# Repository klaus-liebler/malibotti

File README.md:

# Malibotti
Malibotti represents my initial effort to develop a drawing robot, building upon the concepts of the [ESP32-Drawing-Robot project](https://github.com/MatixYo/ESP32-Drawing-Robot). Key differentiators include a reduced reliance on 3D-printed parts and a custom PCB that functions dually as an electronic carrier and a mechanical structure. Additionally, a dedicated daughterboard with high-precision Hall-effect sensors provides servo arm position data, facilitating closed-loop feedback control for 360° servos.

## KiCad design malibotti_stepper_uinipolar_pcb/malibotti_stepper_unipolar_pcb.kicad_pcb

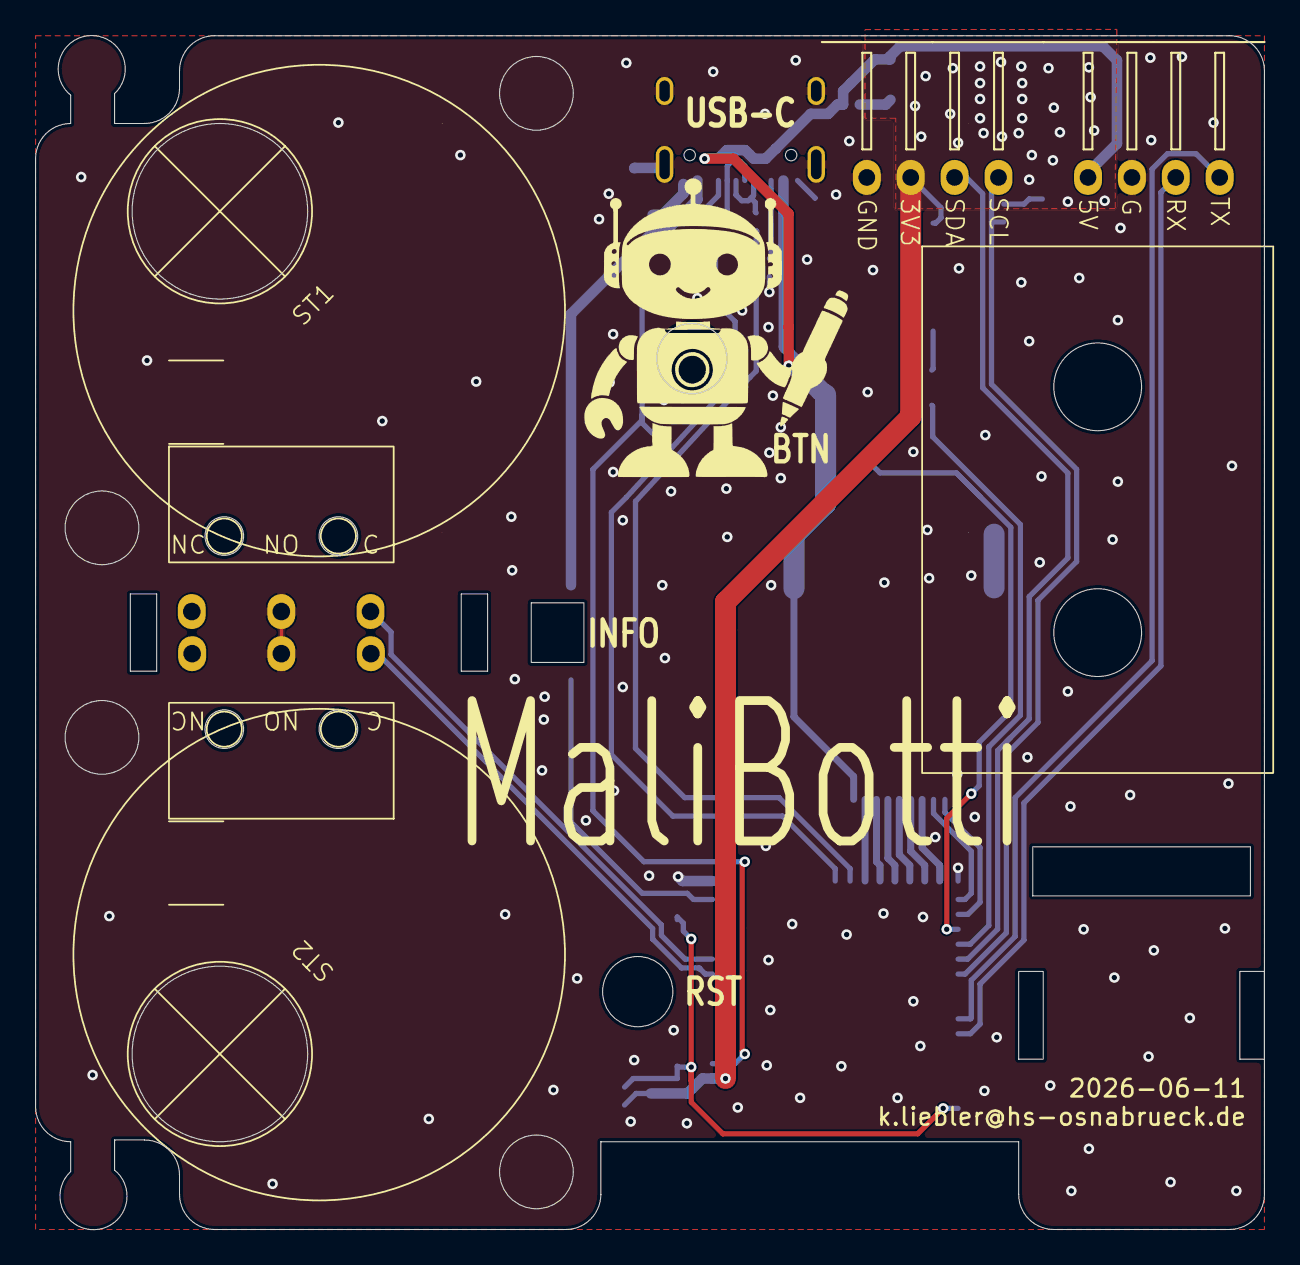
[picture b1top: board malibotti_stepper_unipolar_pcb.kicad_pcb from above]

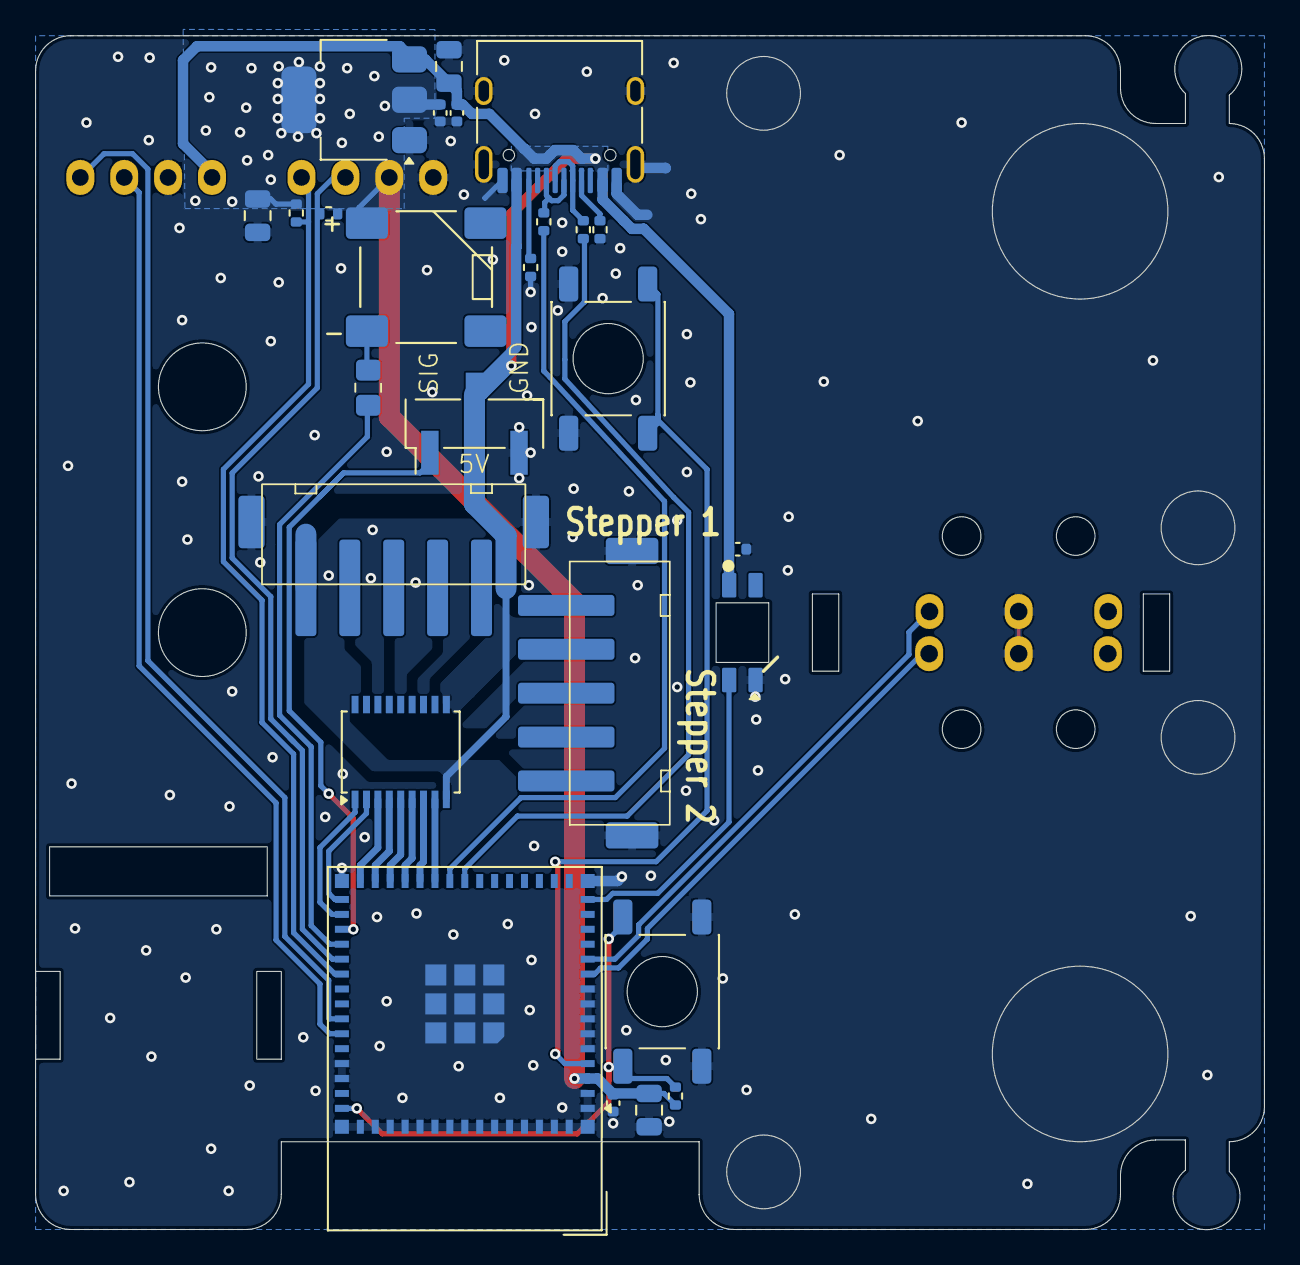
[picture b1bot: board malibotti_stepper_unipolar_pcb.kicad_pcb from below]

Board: 2 copper layers, 70.0 x 68.0 mm, 34 parts (26 on the bottom side), 37 nets.

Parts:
BZ1: Buzzer; XDCR_CMT-7525-80-SMT-TR_handsolder
C3, C9, C10, C11: u1; C_0402_1005Metric
C5, C6, C12: 22u; C_0805_2012Metric
D21: RGB3; SK6812MINI-E_REV
H1: Hinge3040; Hinge_3040
J1: Stepper 1; JST_XH_5P_SMD
J2: Stepper 2; JST_XH_5P_SMD
J3: Servo; PinHeader_1x03_P2.54mm_Vertical_SMD_Pin1Left
J4: I2C; JST_XH_S4B-XH-A-1_1x04_P2.50mm_Horizontal_SmallerCourtyard
J5: USB_C_Receptacle_USB2.0_16P; USB_C_Receptacle_HRO_TYPE-C-31-M-12
J6: Serial; JST_XH_S4B-XH-A-1_1x04_P2.50mm_Horizontal_SmallerCourtyard
R1, R3, R4, R7, R26: 5k1; R_0402_1005Metric
R2: 100R; R_0805_2012Metric_Pad1.20x1.40mm_HandSolder
R8, R9: 22R; R_0402_1005Metric
SRV1: Servo SG90; SG90_vertical_PCB
ST1: Stepper 1; 28BYJ-48
ST2: Stepper 2; 28BYJ-48
SW1: RST; SW_Push_1P1T_NO_6x6mm_H6.5mm_Reverse
SW2: MicroSwitchLeft; Omron D2F Left Angled
SW3: MicroSwitchRight; Omron D2F Right Angled
SW8: BTN; SW_Push_1P1T_NO_6x6mm_H6.5mm_Reverse
U1: TBD62783A; SSOP-18_4.4x6.5mm_P0.65mm
U3: AMS1117; SOT-223-3_TabPin2
U5: ESP32-S3-MINI-1; ESP32-S2-MINI-1

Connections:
+3V3: BZ1.P (+), C6.1, C10.1, C11.1, C12.1, J4.3, R3.2, R4.2, R26.2, U3.2 (VO), U5.3 (3V3)
+5V: C3.1, C5.1, C9.1, D21.1 (VDD), J3.2, J5.A4 (VBUS), J5.A9 (VBUS), J5.B4 (VBUS), J5.B9 (VBUS), J6.4, U1.9 (VCC), U3.3 (VI)
/RX: J6.2, U5.40 (RXD0)
/TX: J6.1, U5.39 (TXD0)
/USBD+: R8.2, U5.24 (USB_D+)
/USBD-: R9.2, U5.23 (USB_D-)
BUZZER: R2.2, U5.34 (IO38)
GND: C3.2, C5.2, C6.2, C9.2, C10.2, C11.2, C12.2, D21.3 (GND), J1.1, J1.MP (MountPin), J2.1, J2.MP (MountPin), J3.3, J4.4, J5.A1 (GND), J5.A12 (GND), J5.B1 (GND), J5.B12 (GND), J5.SH (SHIELD), J6.3, R1.2, R7.2, SW1.2, SW2.2 (C), SW3.2 (C), SW8.1, U1.10 (GND), U3.1 (GND), U5.1 (GND), U5.2 (GND), U5.5 (IO1), U5.6 (IO2), U5.7 (IO3), U5.8 (IO4), U5.9 (IO5), U5.42 (GND), U5.43 (GND), U5.46 (GND), U5.47 (GND), U5.48 (GND), U5.49 (GND), U5.50 (GND), U5.51 (GND), U5.52 (GND), U5.53 (GND), U5.54 (GND), U5.55 (GND), U5.56 (GND), U5.57 (GND), U5.58 (GND), U5.59 (GND), U5.60 (GND), U5.61 (GND), U5.62 (GND), U5.63 (GND), U5.64 (GND), U5.65 (GND)
LIMIT_LEFT: SW2.1 (B), U5.11 (IO7)
LIMIT_RIGHT: SW3.1 (B), U5.10 (IO6)
unnamed: BZ1.N (-), R2.1
unnamed: J1.2, U1.17 (O2)
unnamed: J1.3, U1.15 (O4)
unnamed: J1.4, U1.13 (O6)
unnamed: J1.5, U1.11 (O8)
unnamed: J2.2, U1.12 (O7)
unnamed: J2.3, U1.14 (O5)
unnamed: J2.4, U1.16 (O3)
unnamed: J2.5, U1.18 (O1)
unnamed: J5.A5 (CC1), R1.1
unnamed: J5.B5 (CC2), R7.1
unnamed: J5.A6 (D+), J5.B6 (D+), R8.1
unnamed: J5.A7 (D-), J5.B7 (D-), R9.1
unnamed: R26.1, SW1.1, U5.45 (EN)
unnamed: SW8.2, U5.4 (IO0)
RGB_LED: D21.4 (DIN), U5.15 (IO11)
SCL: J4.1, R3.1, U5.36 (IO40)
SDA: J4.2, R4.1, U5.35 (IO39)
STEPPER1_PH1: U1.8 (I8), U5.25 (IO21)
STEPPER1_PH2: U1.6 (I6), U5.27 (IO47)
STEPPER1_PH3: U1.4 (I4), U5.29 (IO34)
STEPPER1_PH4: U1.2 (I2), U5.31 (IO35)
STEPPER2_PH1: U1.1 (I1), U5.32 (IO36)
STEPPER2_PH2: U1.3 (I3), U5.30 (IO48)
STEPPER2_PH3: U1.5 (I5), U5.28 (IO33)
STEPPER2_PH4: U1.7 (I7), U5.26 (IO26)
Servo1: J3.1, U5.33 (IO37)

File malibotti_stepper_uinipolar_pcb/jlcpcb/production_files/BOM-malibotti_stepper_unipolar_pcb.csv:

Comment,Designator,Footprint,LCSC,Quantity
100R,R2,R_0805_2012Metric_Pad1.20x1.40mm_HandSolder,C17408,1
22R,"R8,R9",R_0402_1005Metric,C25092,2
22u,"C12,C5,C6",C_0805_2012Metric,C45783,3
5k1,"R1,R26,R3,R4,R7",R_0402_1005Metric,C25905,5
AMS1117,U3,SOT-223-3_TabPin2,C6186,1
BTN,SW8,SW_Push_1P1T_NO_6x6mm_H6.5mm_Reverse,C541960,1
Buzzer,BZ1,XDCR_CMT-7525-80-SMT-TR_handsolder,C49246950,1
ESP32-S3-MINI-1,U5,ESP32-S2-MINI-1,C2913206,1
RGB3,D21,SK6812MINI-E_REV,C5149201,1
RST,SW1,SW_Push_1P1T_NO_6x6mm_H6.5mm_Reverse,C541960,1
Servo,J3,PinHeader_1x03_P2.54mm_Vertical_SMD_Pin1Left,C5160786,1
Stepper 1,J1,JST_XH_5P_SMD,C7429683,1
Stepper 2,J2,JST_XH_5P_SMD,C7429683,1
TBD62783A,U1,SSOP-18_4.4x6.5mm_P0.65mm,C4153829,1
USB_C_Receptacle_USB2.0_16P,J5,USB_C_Receptacle_HRO_TYPE-C-31-M-12,C165948,1
u1,"C10,C11,C3,C9",C_0402_1005Metric,C1525,4
MicroSwitchLeft,SW2,Omron D2F Left Angled,,1
Serial,J6,JST_XH_S4B-XH-A-1_1x04_P2.50mm_Horizontal_SmallerCourtyard,,1
MicroSwitchRight,SW3,Omron D2F Right Angled,,1
I2C,J4,JST_XH_S4B-XH-A-1_1x04_P2.50mm_Horizontal_SmallerCourtyard,,1

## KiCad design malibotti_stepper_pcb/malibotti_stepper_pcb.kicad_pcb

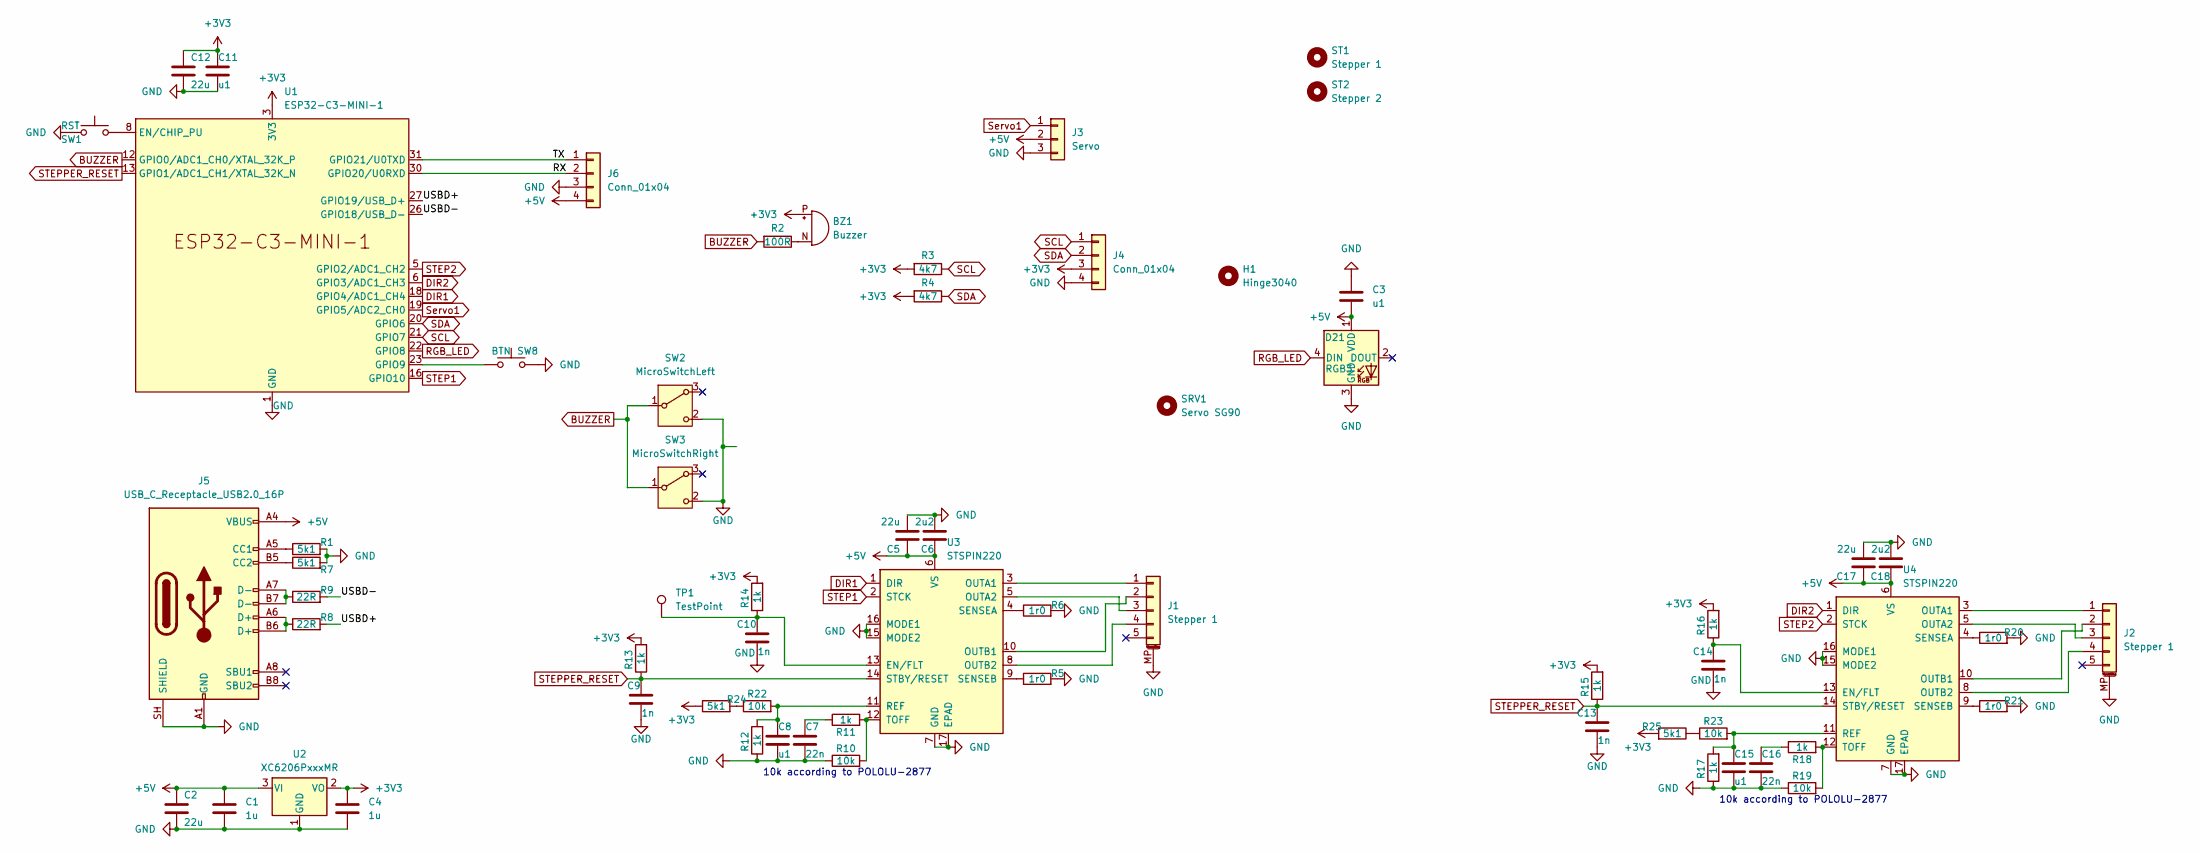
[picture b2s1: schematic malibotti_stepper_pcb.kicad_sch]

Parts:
BZ1: Buzzer; XDCR_CMT-7525-80-SMT-TR_handsolder
C1, C4: 1u; C_0402_1005Metric
C2, C5, C12, C17: 22u; C_0805_2012Metric
C3, C8, C11, C15: u1; C_0402_1005Metric
C6, C18: 2u2; C_0603_1608Metric
C7, C16: 22n; C_0402_1005Metric
C9, C10, C13, C14: 1n; C_0402_1005Metric
D21: RGB3; SK6812MINI-E_REV; MPN SK6812MINI-EA
H1: Hinge3040; Hinge_3040
J1, J2: Stepper 1; JST_XH_5P_SMD
J3: Servo; PinHeader_1x03_P2.54mm_Vertical_SMD_Pin1Left
J4, J6: Conn_01x04; JST_XH_S4B-XH-A-1_1x04_P2.50mm_Horizontal_SmallerCourtyard
J5: USB_C_Receptacle_USB2.0_16P; USB_C_Receptacle_HRO_TYPE-C-31-M-12
R1, R7, R24, R25: 5k1; R_0402_1005Metric
R2: 100R; R_0805_2012Metric_Pad1.20x1.40mm_HandSolder
R3, R4: 4k7; R_0402_1005Metric
R5, R6, R20, R21: 1r0; R_0805_2012Metric_Pad1.20x1.40mm_HandSolder
R8, R9: 22R; R_0402_1005Metric
R10, R19, R22, R23: 10k; R_0402_1005Metric
R11, R12, R13, R14, R15, R16, R17, R18: 1k; R_0402_1005Metric
SRV1: Servo SG90; SG90_vertical_PCB
ST1: Stepper 1; 28BYJ-48
ST2: Stepper 2; 28BYJ-48
SW1: RST; SW_Push_1P1T_NO_6x6mm_H6.5mm_Reverse; MPN TS-1095E-A6B3-D2
SW2: MicroSwitchLeft; Omron D2F Left Angled
SW3: MicroSwitchRight; Omron D2F Right Angled
SW8: BTN; SW_Push_1P1T_NO_6x6mm_H6.5mm_Reverse; MPN TS-1095E-A6B3-D2
TP1: TestPoint; TestPoint_Loop_D1.80mm_Drill1.0mm_Beaded
U1: ESP32-C3-MINI-1
U2: XC6206PxxxMR; SOT-23-3
U3, U4: STSPIN220; VQFN-16-1EP_3x3mm_P0.5mm_EP1.8x1.8mm

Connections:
+3V3: BZ1.P (+), C4.1, C11.1, C12.1, J4.3, R3.2, R4.2, R13.2, R14.2, R15.2, R16.2, R24.1, R25.2, U1.3 (3V3), U2.2 (VO); also elsewhere on the board
+5V: C1.1, C2.1, C3.1, C5.1, C6.1, C17.1, C18.1, D21.1 (VDD), J3.2, J5.A4 (VBUS), J5.A9 (VBUS), J5.B4 (VBUS), J5.B9 (VBUS), J6.4, U2.3 (VI), U3.6 (VS), U4.6 (VS)
/RX: J6.2, U1.30 (GPIO20/U0RXD)
/TX: J6.1, U1.31 (GPIO21/U0TXD)
/USBD+: R8.2, U1.27 (GPIO19/USB_D+)
/USBD-: R9.2, U1.26 (GPIO18/USB_D-)
BUZZER: R2.2, SW2.1 (B), SW3.1 (B), U1.12 (GPIO0/ADC1_CH0/XTAL_32K_P)
DIR1: U1.18 (GPIO4/ADC1_CH4), U3.1 (DIR)
DIR2: U1.6 (GPIO3/ADC1_CH3), U4.1 (DIR)
GND: C1.2, C2.2, C3.2, C4.2, C5.2, C6.2, C7.2, C8.2, C9.2, C10.2, C11.2, C12.2, C13.2, C14.2, C15.2, C16.2, C17.2, C18.2, D21.3 (GND), J1.MP (MountPin), J2.MP (MountPin), J3.3, J4.4, J5.A1 (GND), J5.A12 (GND), J5.B1 (GND), J5.B12 (GND), J5.SH (SHIELD), J6.3, R1.2, R5.2, R6.2, R7.2, R10.1, R12.1, R17.1, R19.1, R20.2, R21.2, SW1.2, SW2.2 (C), SW3.2 (C), SW8.2, U1.1 (GND), U1.2 (GND), U1.11 (GND), U1.14 (GND), U1.36 (GND), U1.37 (GND), U1.38 (GND), U1.39 (GND), U1.40 (GND), U1.41 (GND), U1.42 (GND), U1.43 (GND), U1.44 (GND), U1.45 (GND), U1.46 (GND), U1.47 (GND), U1.48 (GND), U1.49 (GND), U1.50 (GND), U1.51 (GND), U1.52 (GND), U1.53 (GND), U2.1 (GND), U3.7 (GND), U3.15 (MODE2), U3.16 (MODE1), U3.17 (EPAD), U4.7 (GND), U4.15 (MODE2), U4.16 (MODE1), U4.17 (EPAD)
unnamed: BZ1.N (-), R2.1
unnamed: C7.1, R11.1
unnamed: C16.1, R18.1
unnamed: J1.1, U3.3 (OUTA1)
unnamed: J1.2, U3.10 (OUTB1)
unnamed: J1.3, U3.5 (OUTA2)
unnamed: J1.4, U3.8 (OUTB2)
unnamed: J2.1, U4.3 (OUTA1)
unnamed: J2.2, U4.10 (OUTB1)
unnamed: J2.3, U4.5 (OUTA2)
unnamed: J2.4, U4.8 (OUTB2)
unnamed: J5.A5 (CC1), R1.1
unnamed: J5.B5 (CC2), R7.1
unnamed: J5.A6 (D+), J5.B6 (D+), R8.1
unnamed: J5.A7 (D-), J5.B7 (D-), R9.1
unnamed: R22.1, R24.2
unnamed: R23.1, R25.1
unnamed 27: SW1.1, U1.8 (EN/CHIP_PU); also elsewhere on the board
unnamed: SW8.1, U1.23 (GPIO9)
unnamed: C10.1, R14.1, TP1.1 (1_1), U3.13 (EN/FLT)
unnamed: C8.1, R12.2, R22.2, U3.11 (REF)
unnamed: R6.1, U3.4 (SENSEA)
unnamed: R5.1, U3.9 (SENSEB)
unnamed: R10.2, R11.2, U3.12 (TOFF)
unnamed: C14.1, R16.1, U4.13 (EN/FLT)
unnamed: C15.1, R17.2, R23.2, U4.11 (REF)
unnamed: R20.1, U4.4 (SENSEA)
unnamed: R21.1, U4.9 (SENSEB)
unnamed: R18.2, R19.2, U4.12 (TOFF)
RGB_LED: D21.4 (DIN), U1.22 (GPIO8)
SCL: J4.1, R3.1, U1.21 (GPIO7)
SDA: J4.2, R4.1, U1.20 (GPIO6)
STEP1: U1.16 (GPIO10), U3.2 (STCK)
STEP2: U1.5 (GPIO2/ADC1_CH2), U4.2 (STCK)
STEPPER_RESET: C9.1, C13.1, R13.1, R15.1, U1.13 (GPIO1/ADC1_CH1/XTAL_32K_N), U3.14 (STBY/RESET), U4.14 (STBY/RESET)
Servo1: J3.1, U1.19 (GPIO5/ADC2_CH0)

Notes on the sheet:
10k according to POLOLU-2877

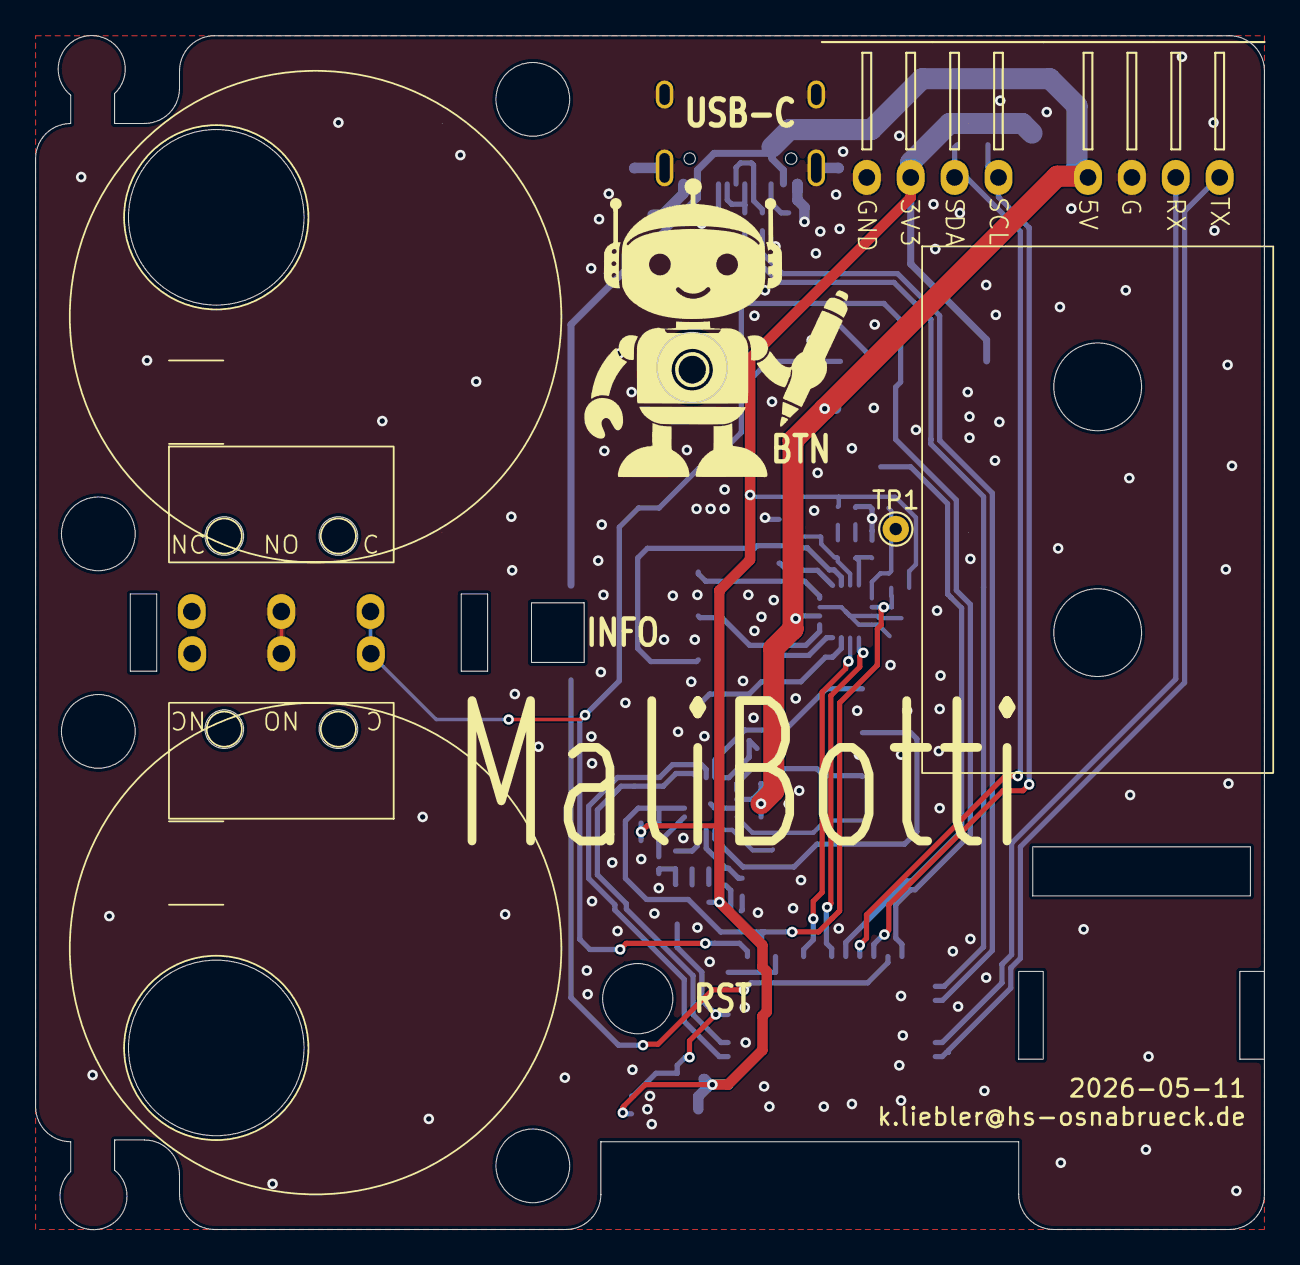
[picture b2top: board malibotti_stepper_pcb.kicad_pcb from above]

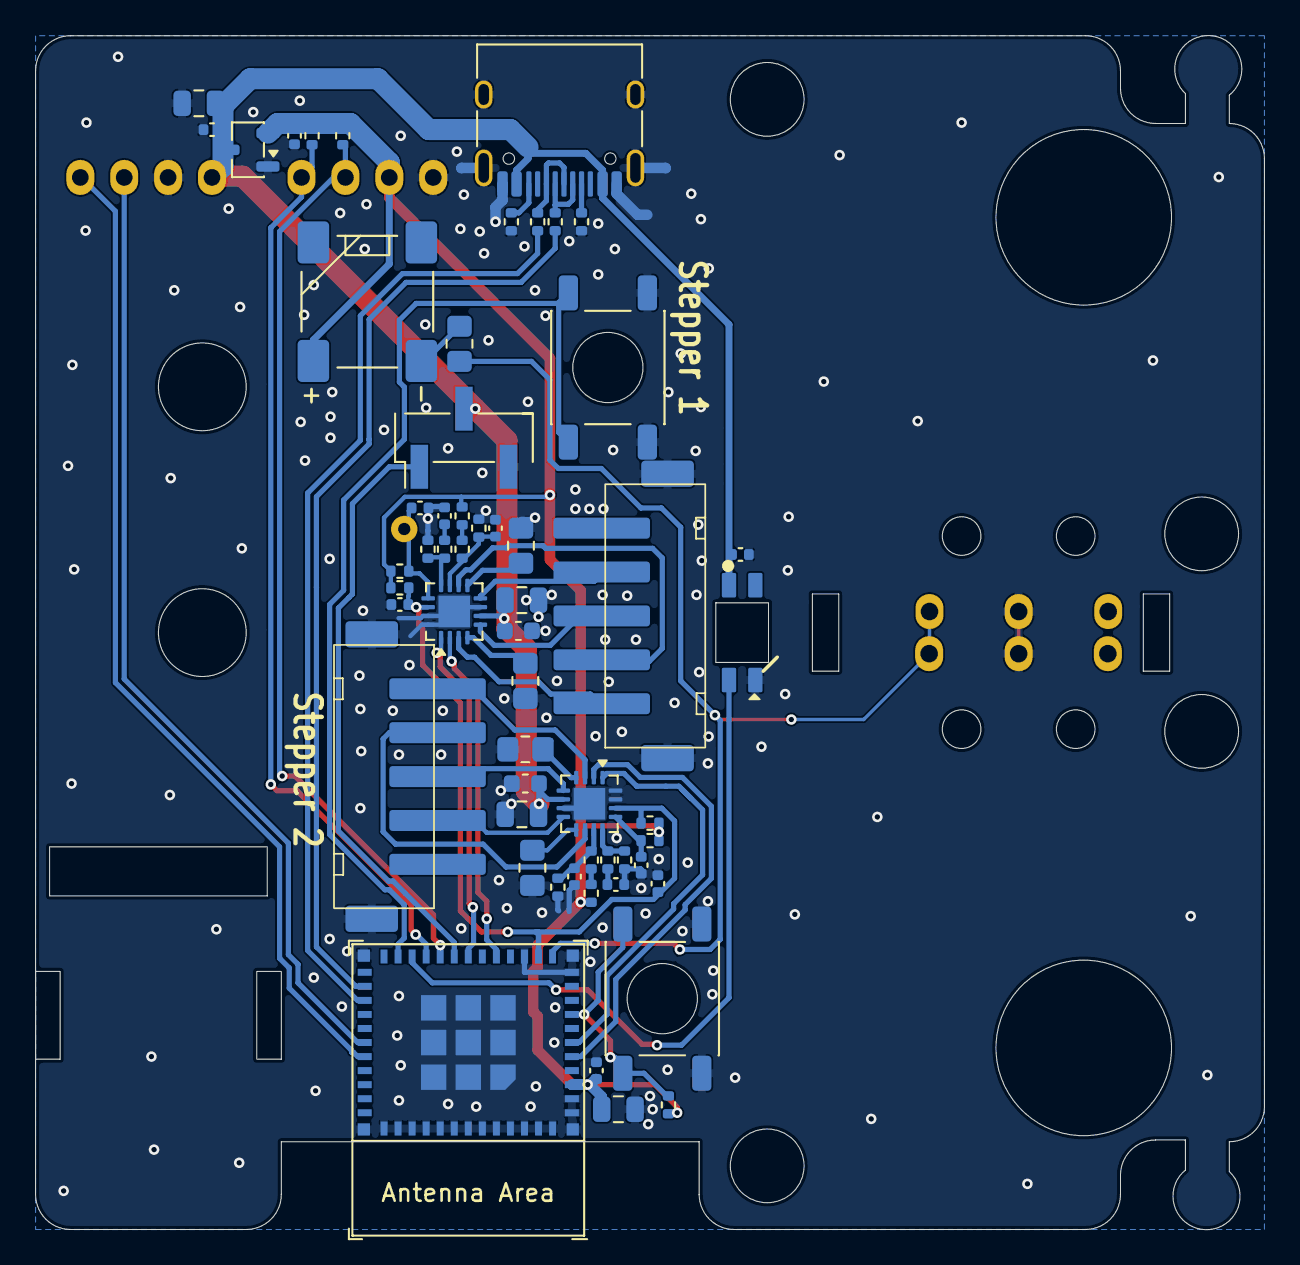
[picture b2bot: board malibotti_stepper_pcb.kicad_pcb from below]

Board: 2 copper layers, 70.0 x 68.0 mm, 65 parts (55 on the bottom side), 46 nets.

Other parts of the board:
R26: 10k; R_0402_1005Metric

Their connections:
+3V3: R26.2; also elsewhere on the board
unnamed 27: R26.1; also elsewhere on the board

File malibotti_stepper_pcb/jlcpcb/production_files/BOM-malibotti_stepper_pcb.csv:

Comment,Designator,Footprint,LCSC,Quantity
100R,R2,R_0805_2012Metric_Pad1.20x1.40mm_HandSolder,C17408,1
10k,"R10,R19,R22,R23",R_0402_1005Metric,C25744,4
1k,"R11,R12,R13,R14,R15,R16,R17,R18",R_0402_1005Metric,C11702,8
1n,"C10,C13,C14,C9",C_0402_1005Metric,C1523,4
1r0,"R20,R21,R5,R6",R_0805_2012Metric_Pad1.20x1.40mm_HandSolder,C25271,4
1u,"C1,C4",C_0402_1005Metric,C52923,2
22R,"R8,R9",R_0402_1005Metric,C25092,2
22n,"C16,C7",C_0402_1005Metric,C1532,2
22u,"C12,C17,C2,C5",C_0805_2012Metric,C45783,4
2u2,"C18,C6",C_0603_1608Metric,C23630,2
4k7,"R3,R4",R_0402_1005Metric,C25900,2
5k1,"R1,R24,R25,R7",R_0402_1005Metric,C25905,4
BTN,SW8,SW_Push_1P1T_NO_6x6mm_H6.5mm_Reverse,C541960,1
Buzzer,BZ1,XDCR_CMT-7525-80-SMT-TR_handsolder,C49246950,1
ESP32-C3-MINI-1,U1,ESP32-C3-MINI-1,C2838502,1
RGB3,D21,SK6812MINI-E_REV,C5149201,1
RST,SW1,SW_Push_1P1T_NO_6x6mm_H6.5mm_Reverse,C541960,1
STSPIN220,"U3,U4",VQFN-16-1EP_3x3mm_P0.5mm_EP1.8x1.8mm,C2150516,2
Servo,J3,PinHeader_1x03_P2.54mm_Vertical_SMD_Pin1Left,C5160786,1
Stepper 1,"J1,J2",JST_XH_5P_SMD,C7429683,2
USB_C_Receptacle_USB2.0_16P,J5,USB_C_Receptacle_HRO_TYPE-C-31-M-12,C165948,1
XC6206PxxxMR,U2,SOT-23-3,C5446,1
u1,"C11,C15,C3,C8",C_0402_1005Metric,C1525,4
MicroSwitchLeft,SW2,Omron D2F Left Angled,,1
Conn_01x04,J6,JST_XH_S4B-XH-A-1_1x04_P2.50mm_Horizontal_SmallerCourtyard,,1
MicroSwitchRight,SW3,Omron D2F Right Angled,,1
Conn_01x04,J4,JST_XH_S4B-XH-A-1_1x04_P2.50mm_Horizontal_SmallerCourtyard,,1
TestPoint,TP1,TestPoint_THTPad_D1.0mm_Drill0.5mm,,1

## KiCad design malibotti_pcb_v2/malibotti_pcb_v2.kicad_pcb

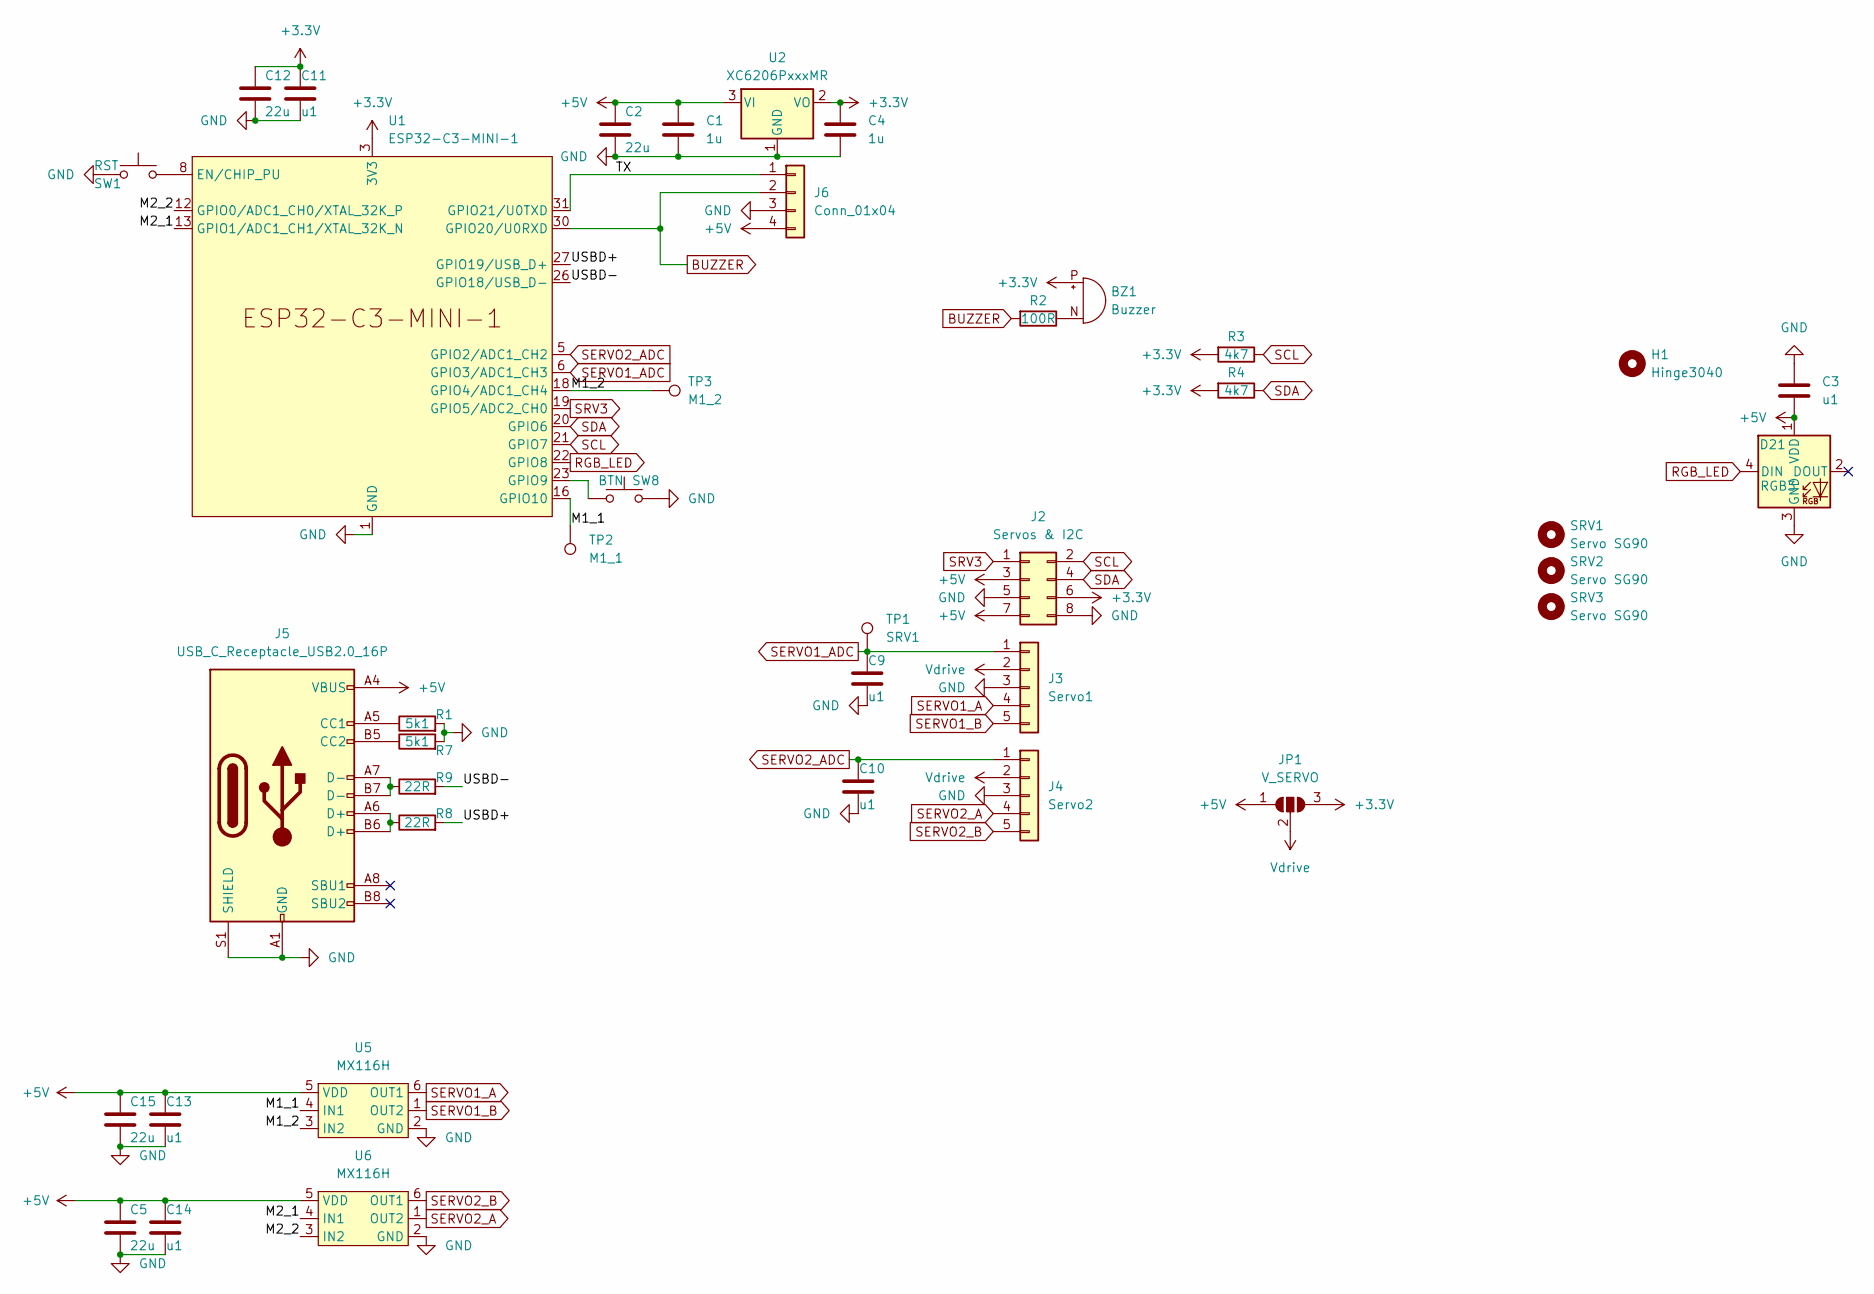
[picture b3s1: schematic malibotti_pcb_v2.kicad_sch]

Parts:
BZ1: Buzzer; XDCR_CMT-7525-80-SMT-TR_handsolder
C1, C4: 1u; C_0402_1005Metric
C2, C5, C12, C15: 22u; C_0603_1608Metric
C3, C11, C13, C14: u1; C_0402_1005Metric
C9, C10: u1; C_0805_2012Metric_Pad1.18x1.45mm_HandSolder
D21: RGB3; SK6812MINI-E_REV; MPN SK6812MINI-EA
H1: Hinge3040; Hinge_3040
J2: Servos & I2C; PinHeader_2x04_P2.54mm_Vertical_SMD
J3: Servo1; JST_XH_B5B-XH-A_1x05_P2.50mm_Vertical
J4: Servo2; JST_XH_B5B-XH-A_1x05_P2.50mm_Vertical
J5: USB_C_Receptacle_USB2.0_16P; USB_C_Receptacle_HRO_TYPE-C-31-M-12
J6: Conn_01x04; JST_XH_S4B-XH-A-1_1x04_P2.50mm_Horizontal_SmallerCourtyard
JP1: V_SERVO; SolderJumper-3_P1.3mm_Bridged2Bar12_RoundedPad1.0x1.5mm_Num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
R1, R7: 5k1; R_0402_1005Metric
R2: 100R; R_0805_2012Metric_Pad1.20x1.40mm_HandSolder
R3, R4: 4k7; R_0402_1005Metric
R8, R9: 22R; R_0402_1005Metric
SRV1, SRV2: Servo SG90; SG90_PCB
SRV3: Servo SG90; SG90_vertical_PCB
SW1: RST; SW_Push_1P1T_NO_6x6mm_H6.5mm_Reverse; MPN TS-1095E-A6B3-D2
SW8: BTN; SW_Push_1P1T_NO_6x6mm_H6.5mm_Reverse; MPN TS-1095E-A6B3-D2
TP1: SRV1; TestPoint_Pad_1.5x1.5mm
TP2: M1_1; TestPoint_Pad_1.5x1.5mm
TP3: M1_2; TestPoint_Pad_1.5x1.5mm
U1: ESP32-C3-MINI-1
U2: XC6206PxxxMR; SOT-23-3
U5, U6: MX116H; SOT-23-6

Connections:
+3.3V: BZ1.P (+), C4.1, C11.1, C12.1, J2.6, JP1.3 (B), R3.2, R4.2, U1.3 (3V3), U2.2 (VO)
+5V: C1.1, C2.1, C3.1, C5.1, C13.1, C14.1, C15.1, D21.1 (VDD), J2.3, J2.7, J5.A4 (VBUS), J5.A9 (VBUS), J5.B4 (VBUS), J5.B9 (VBUS), J6.4, JP1.1 (A), U2.3 (VI), U5.5 (VDD), U6.5 (VDD)
/M1_1: TP2.1, U1.16 (GPIO10), U5.4 (IN1)
/M1_2: TP3.1, U1.18 (GPIO4/ADC1_CH4), U5.3 (IN2)
/M2_1: U1.13 (GPIO1/ADC1_CH1/XTAL_32K_N), U6.4 (IN1)
/M2_2: U1.12 (GPIO0/ADC1_CH0/XTAL_32K_P), U6.3 (IN2)
/TX: J6.1, U1.31 (GPIO21/U0TXD)
/USBD+: R8.2, U1.27 (GPIO19/USB_D+)
/USBD-: R9.2, U1.26 (GPIO18/USB_D-)
BUZZER: J6.2, R2.2, U1.30 (GPIO20/U0RXD)
GND: C1.2, C2.2, C3.2, C4.2, C5.2, C9.2, C10.2, C11.2, C12.2, C13.2, C14.2, C15.2, D21.3 (GND), J2.5, J2.8, J3.3, J4.3, J5.A1 (GND), J5.A12 (GND), J5.B1 (GND), J5.B12 (GND), J5.S1 (SHIELD), J6.3, R1.2, R7.2, SW1.2, SW8.2, U1.1 (GND), U1.2 (GND), U1.11 (GND), U1.14 (GND), U1.36 (GND), U1.37 (GND), U1.38 (GND), U1.39 (GND), U1.40 (GND), U1.41 (GND), U1.42 (GND), U1.43 (GND), U1.44 (GND), U1.45 (GND), U1.46 (GND), U1.47 (GND), U1.48 (GND), U1.49 (GND), U1.50 (GND), U1.51 (GND), U1.52 (GND), U1.53 (GND), U2.1 (GND), U5.2 (GND), U6.2 (GND)
unnamed: BZ1.N (-), R2.1
unnamed: J5.A5 (CC1), R1.1
unnamed: J5.B5 (CC2), R7.1
unnamed: J5.A6 (D+), J5.B6 (D+), R8.1
unnamed: J5.A7 (D-), J5.B7 (D-), R9.1
unnamed: SW1.1, U1.8 (EN/CHIP_PU)
unnamed: SW8.1, U1.23 (GPIO9)
RGB_LED: D21.4 (DIN), U1.22 (GPIO8)
SCL: J2.2, R3.1, U1.21 (GPIO7)
SDA: J2.4, R4.1, U1.20 (GPIO6)
SERVO1_A: J3.4, U5.6 (OUT1)
SERVO1_ADC: C9.1, J3.1, TP1.1, U1.6 (GPIO3/ADC1_CH3)
SERVO1_B: J3.5, U5.1 (OUT2)
SERVO2_A: J4.4, U6.1 (OUT2)
SERVO2_ADC: C10.1, J4.1, U1.5 (GPIO2/ADC1_CH2)
SERVO2_B: J4.5, U6.6 (OUT1)
SRV3: J2.1, U1.19 (GPIO5/ADC2_CH0)
Vdrive: J3.2, J4.2, JP1.2 (C)

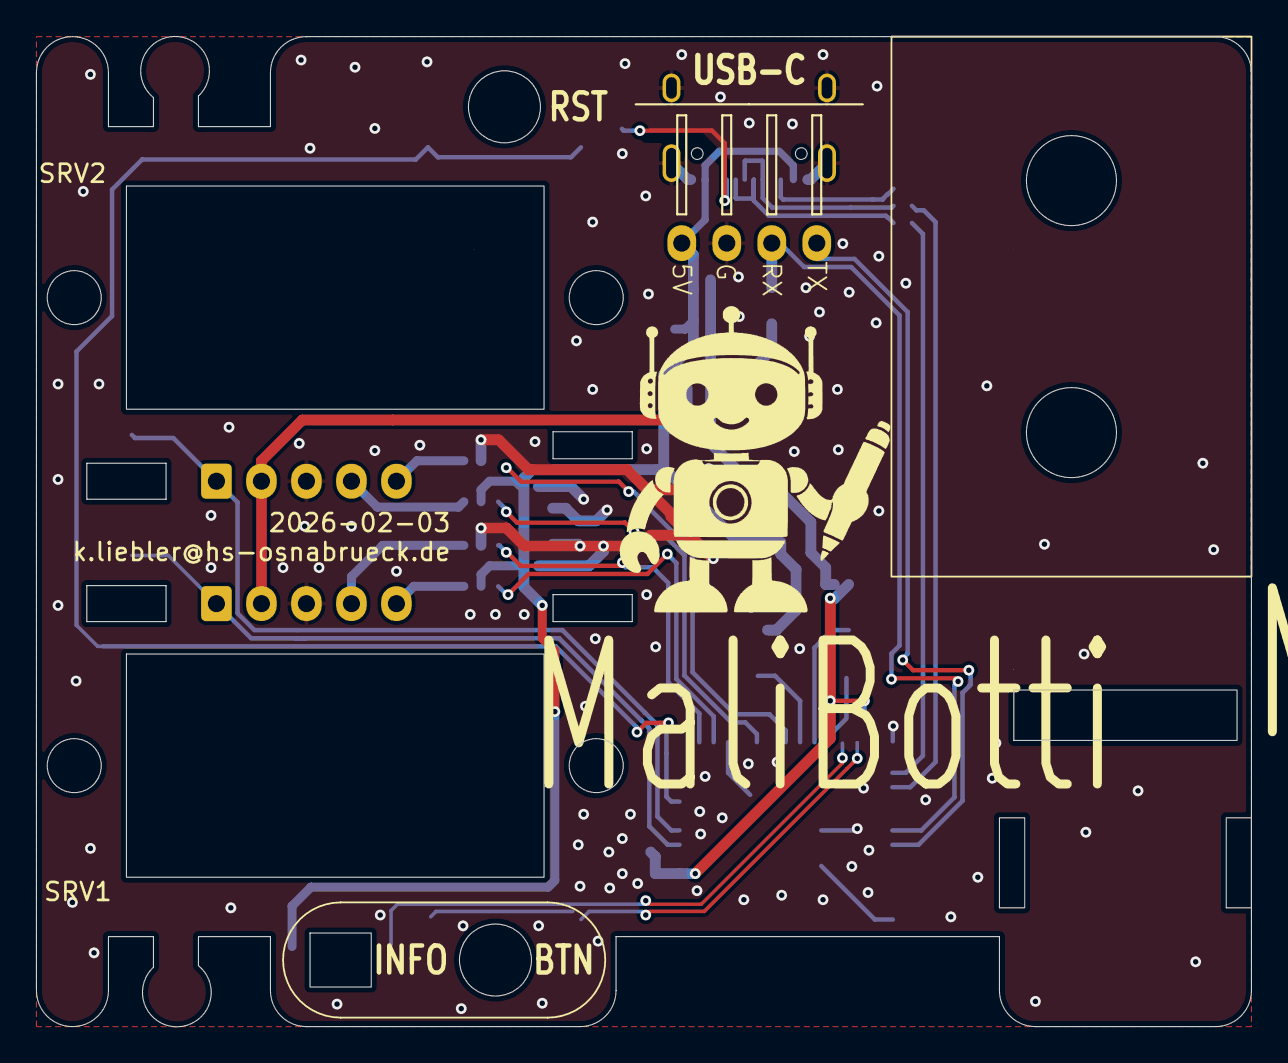
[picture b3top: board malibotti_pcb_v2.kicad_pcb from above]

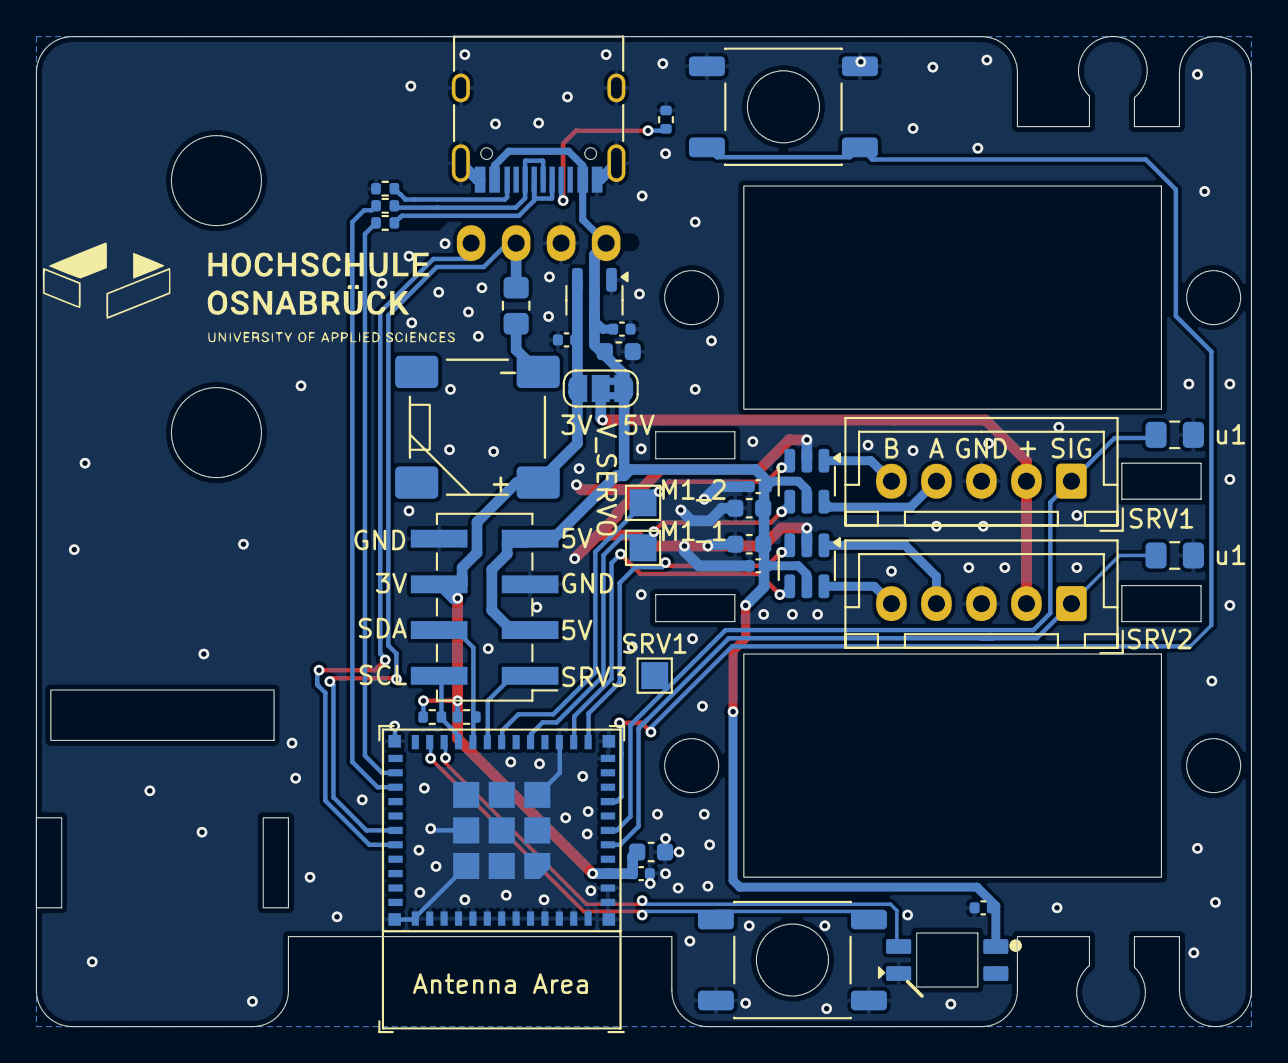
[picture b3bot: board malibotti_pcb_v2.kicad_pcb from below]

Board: 2 copper layers, 67.5 x 55.0 mm, 40 parts (34 on the bottom side), 29 nets.
